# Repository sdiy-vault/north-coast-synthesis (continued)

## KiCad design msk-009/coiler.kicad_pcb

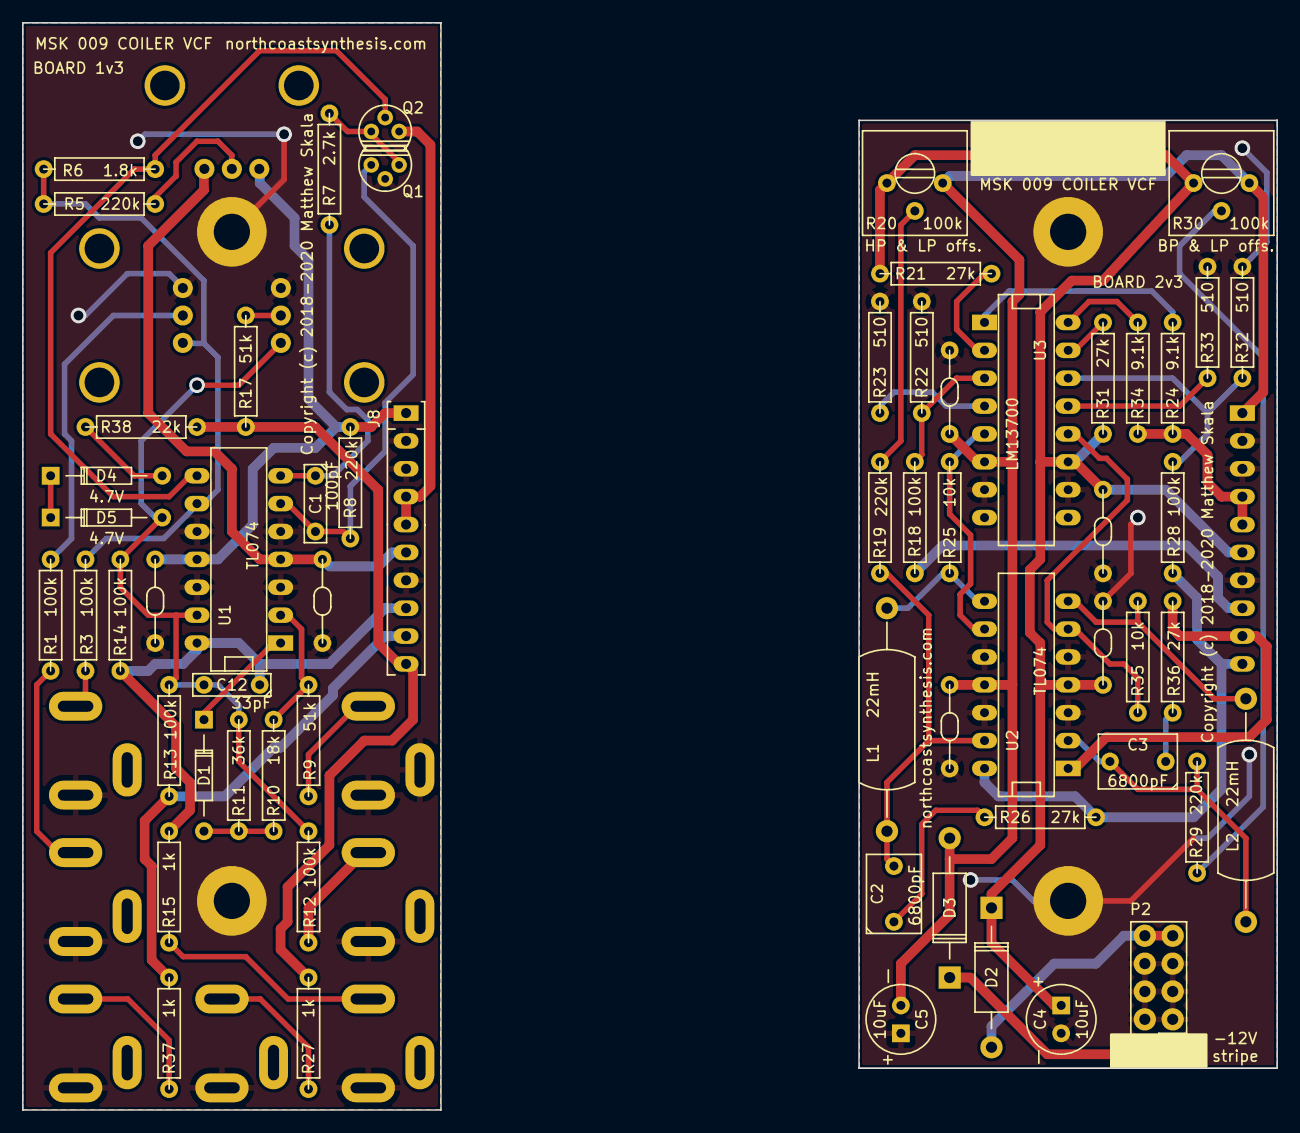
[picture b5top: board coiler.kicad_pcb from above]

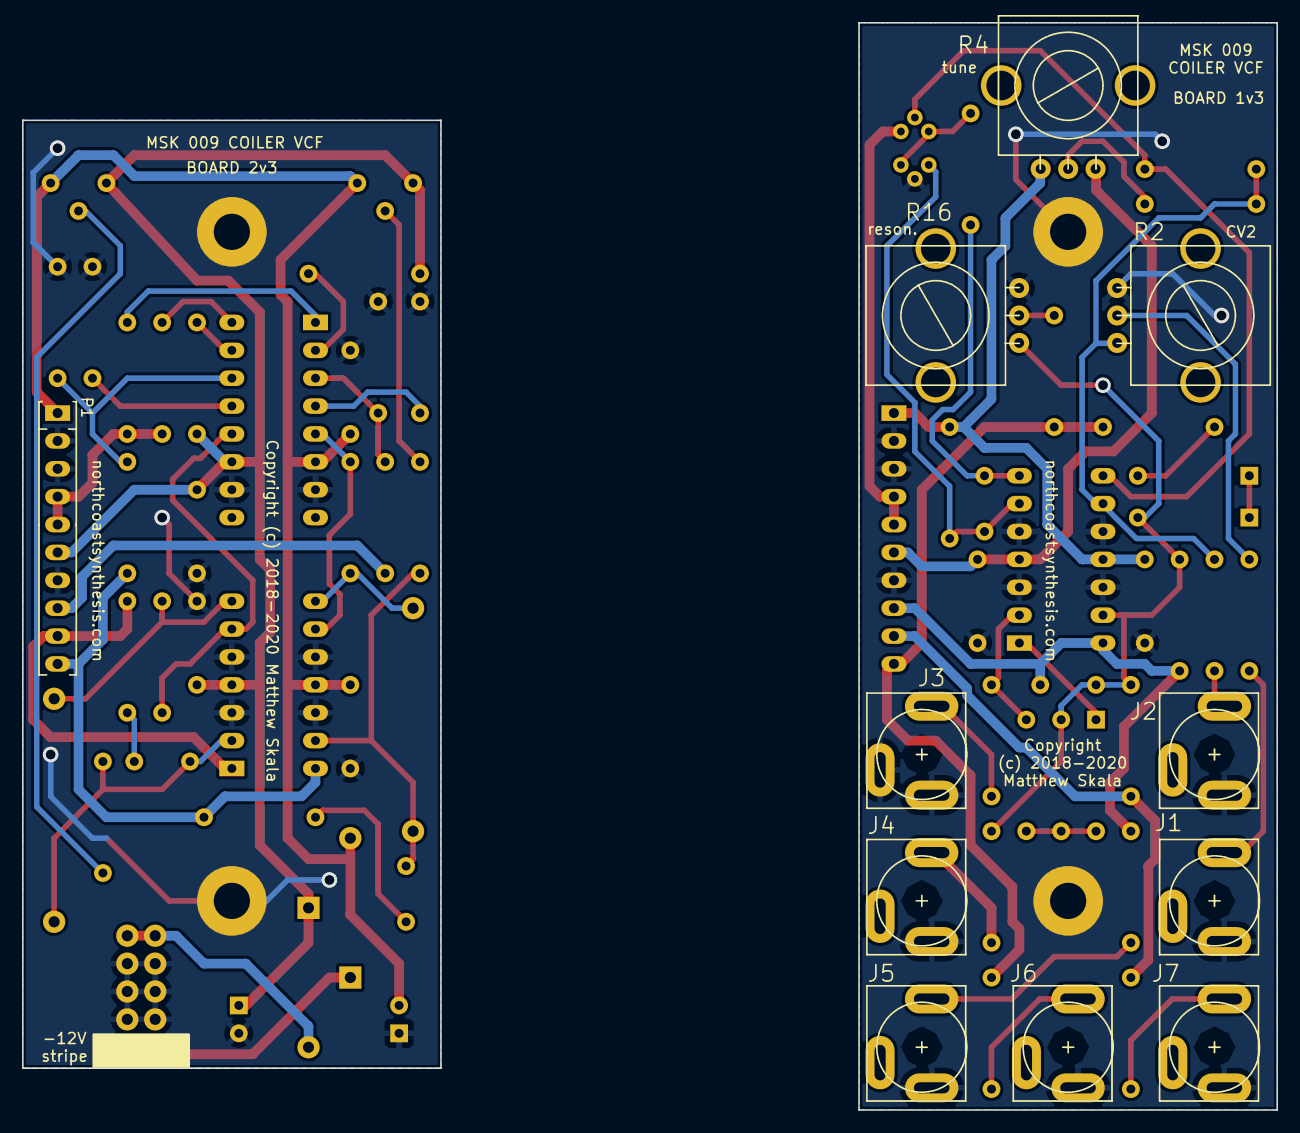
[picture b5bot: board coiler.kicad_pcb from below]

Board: 2 copper layers, 114.3 x 99.1 mm, 76 parts (11 on the bottom side), 48 nets.

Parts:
C1: 100pF; C2msk
C2, C3: 6800pF; C2_3x2msk
C4, C5: 10uF; C1V7msk
C6, C7, C8, C9, C10, C11: 0.1uF; C3msk
C12: 33pF; C2msk
D1: 1N4148; DO35msk
D2, D3: 1N5818; DO15msk
D4, D5: 1N5230B; DO35msk
H5, H6, H9, H10: CONN_01X01; MountingHole_M3
J1, J2, J3, J4, J5, J6, J7: 1502 03; mono_jack_slotted
J8: CONN_01X10; SIP10-socket
L1, L2: 22mH; L8msk
P1: CONN_01X10; SIP10-pins
P2: CONN_02X05; 2x05msk
Q1, Q2: SS8550D; TO92Xmsk
R1, R3, R12, R13, R14, R18, R28: 100k; R4valmsk
R2, R4, R16: 100k; P260Tpot
R5, R8, R19, R29: 220k; R4valmsk
R6: 1.8k; R4valmsk
R7: 2.7k; R4valmsk
R9, R17: 51k; R4valmsk
R10: 18k; R4valmsk
R11: 36k; R4valmsk
R15, R27, R37: 1k; R4valmsk
R20, R30: 100k; 3386Pmsk
R21, R26, R31, R36: 27k; R4valmsk
R22, R23, R32, R33: 510; R4valmsk
R24, R34: 9.1k; R4valmsk
R25, R35: 10k; R4valmsk
R38: 22k; R4valmsk
U1, U2: TL074; DIP14msk
U3: LM13700; DIP16msk

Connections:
+12V: C4.1, C6.2, C8.1, C10.2, D2.2 (K), J8.6, P1.6, R4.3, R20.1, R21.1, R30.1, R31.1, U1.4 (V+), U2.4 (V+), U3.11
-12V: C5.2, C7.2, C9.2, C11.2, D3.1 (A), J8.1, P1.1, R4.1, R8.2, R20.3, R30.3, U1.11 (V-), U2.11 (V-), U3.6 (V-)
/BP: J8.10, P1.10, R17.2, R26.1, R27.2, R28.2, R38.2, U2.14
/CC: J8.4, J8.5, P1.4, P1.5, Q2.3 (C), R24.1, R34.1
/HP: C12.1, J8.8, P1.8, R14.1, R15.2, R18.2, U1.14
/LP: J8.9, P1.9, R13.2, R36.1, R37.2, U2.1
GNDREF: C4.2, C5.1, C6.1, C7.1, C8.2, C9.1, C10.1, C11.1, H5.1, H6.1, H9.1, H10.1, J1.3, J2.3, J3.2, J3.3, J4.3, J5.3, J6.3, J7.3, J8.2, J8.3, J8.7, P1.2, P1.3, P1.7, P2.3, P2.4, P2.5, P2.6, P2.7, P2.8, Q1.2 (B), R2.1, R16.3, R22.2, R23.2, R32.2, R33.2, U1.3 (+), U1.5 (+), U1.10 (+), U1.12 (+), U2.3 (+), U2.5 (+), U2.10 (+), U2.12 (+), U3.7, U3.10
unnamed: C1.1, R7.2, U1.7
unnamed: C1.2, Q1.3 (C), R8.1, U1.6 (-)
unnamed: C2.1, R26.2
unnamed: C2.2, L1.2, R19.1, U2.13 (-)
unnamed: C3.1, R36.2
unnamed: C3.2, L2.2, R29.1, U2.2 (-)
unnamed: C12.2, D5.1 (A), R11.2, R12.1, R13.1, R14.2, R16.1, U1.13 (-)
unnamed: D1.1 (A), R10.1, R11.1
unnamed: D1.2 (K), U1.1
unnamed: D2.1 (A), P2.9, P2.10
unnamed: D3.2 (K), P2.1, P2.2
unnamed: D4.1 (A), R38.1
unnamed: D4.2 (K), D5.2 (K)
unnamed: J1.1, R1.2
unnamed: J2.1, R3.2
unnamed: J3.1, R9.2
unnamed: J4.1, R12.2
unnamed: J5.1, R15.1
unnamed: J6.1, R27.1
unnamed: J7.1, R37.1
unnamed: L1.1, R25.1, U2.8
unnamed: L2.1, R35.1, U2.7
unnamed: Q1.1 (E), Q2.1 (E), R7.1
unnamed: Q2.2 (B), R6.1, U1.8
unnamed: R1.1, R2.2
unnamed: R2.3, R3.1, R5.1, R6.2, U1.9 (-)
unnamed: R4.2, R5.2
unnamed: R9.1, R10.2, U1.2 (-)
unnamed: R16.2, R17.1
unnamed: R18.1, R22.1, U3.3 (+)
unnamed: R19.2, R20.2
unnamed: R21.2, U3.2 (Ibias)
unnamed: R23.1, U3.4 (-)
unnamed: R24.2, U3.1
unnamed: R25.2, U2.9 (-), U3.5
unnamed: R28.1, R32.1, U3.14 (+)
unnamed: R29.2, R30.2
unnamed: R31.2, U3.15 (Ibias)
unnamed: R33.1, U3.13 (-)
unnamed: R34.2, U3.16
unnamed: R35.2, U2.6 (-), U3.12

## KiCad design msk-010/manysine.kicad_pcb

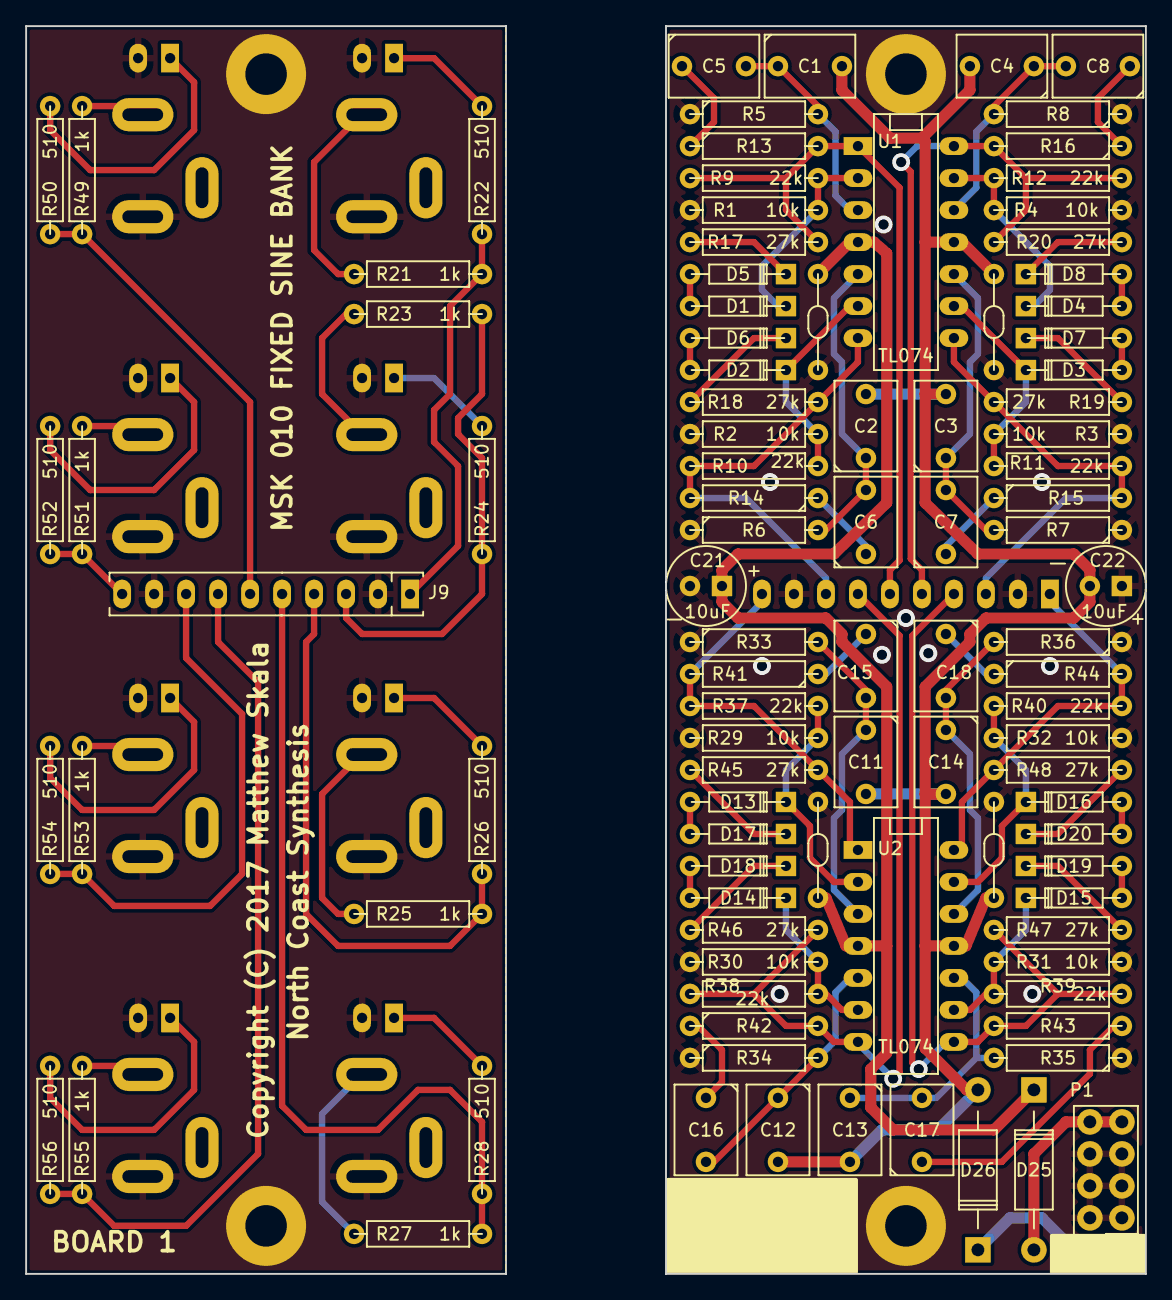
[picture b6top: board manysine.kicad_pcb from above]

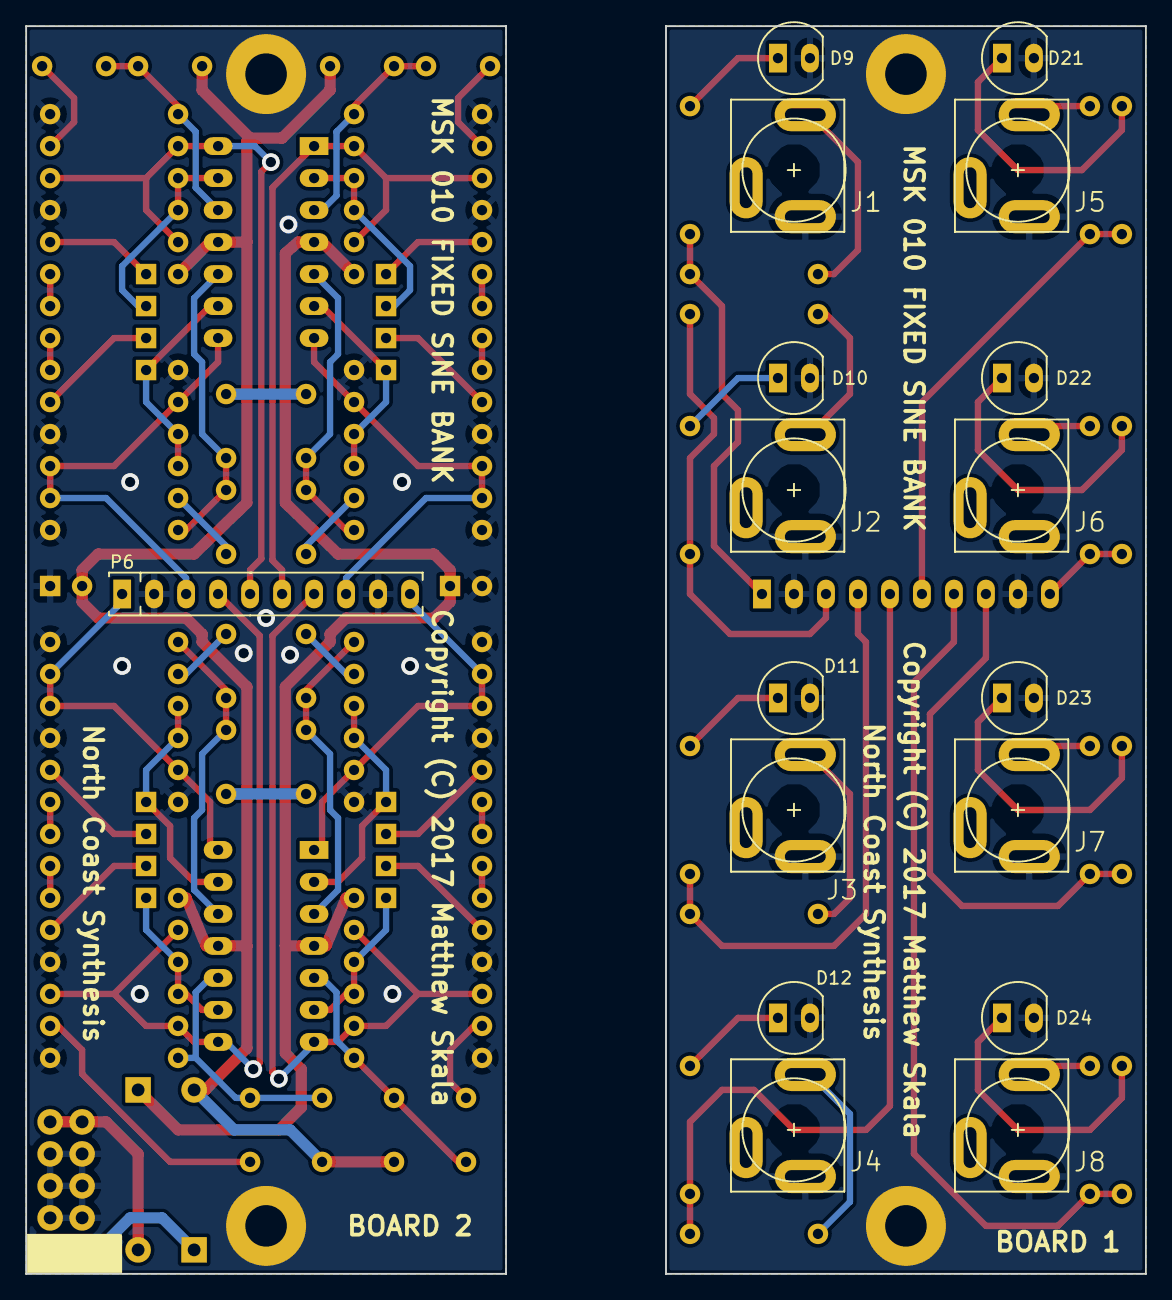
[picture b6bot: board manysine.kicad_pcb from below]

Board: 2 copper layers, 88.9 x 99.1 mm, 121 parts (17 on the bottom side), 69 nets.

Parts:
C1, C2, C3, C4, C5, C6, C7, C8, C11, C12, C13, C14, C15, C16, C17, C18: C; C2_3x2msk
C9, C10, C19, C20: 0.1uF; C3msk
C21, C22: 10uF; C1V7msk
D1, D2, D3, D4, D5, D6, D7, D8, D13, D14, D15, D16, D17, D18, D19, D20: 1N5229B; DO35_3msk
D9, D10, D11, D12, D21, D22, D23, D24: L-57EGW; LEDmsk
D25, D26: 1N5818; DO15msk
H15, H16, H19, H20: CONN_01X01; MountingHole_M3
J1, J2, J3, J4, J5, J6, J7, J8: 1502 03; mono_jack_slotted
J9: CONN_01X10; SIP10msk
P1: CONN_02X05; 2x05msk
P6: CONN_01X10; SIP10msk
R1, R2, R3, R4, R29, R30, R31, R32: 10k; R4valmsk
R5, R6, R7, R8, R13, R14, R15, R16, R33, R34, R35, R36, R41, R42, R43, R44: R; R4msk
R9, R10, R11, R12, R37, R38, R39, R40: 22k; R4valmsk
R17, R18, R19, R20, R45, R46, R47, R48: 27k; R4valmsk
R21, R23, R25, R27, R49, R51, R53, R55: 1k; R4valmsk
R22, R24, R26, R28, R50, R52, R54, R56: 510; R4valmsk
U1, U2: TL074; DIP14msk

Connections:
+12V: C9.2, C19.2, C21.1, D25.2 (K), U1.4 (V+), U2.4 (V+)
-12V: C1.2, C2.2, C3.2, C4.2, C10.2, C11.2, C12.2, C13.2, C14.2, C20.2, C22.2, D26.1 (A), U1.11 (V-), U2.11 (V-)
/OSCA: J9.6, P6.6, R9.2, R13.2, R17.2, R49.1, R50.1, U1.1
/OSCB: J9.8, P6.8, R10.2, R14.2, R18.2, R53.1, R54.1, U1.7
/OSCC: J9.3, P6.3, R11.2, R15.2, R19.2, R23.1, R24.1, U1.8
/OSCD: J9.5, P6.5, R12.2, R16.2, R20.2, R27.1, R28.1, U1.14
/OSCE: J9.10, P6.10, R37.2, R41.2, R45.2, R51.1, R52.1, U2.1
/OSCF: J9.7, P6.7, R38.2, R42.2, R46.2, R55.1, R56.1, U2.7
/OSCG: J9.4, P6.4, R25.1, R26.1, R39.2, R43.2, R47.2, U2.8
/OSCH: J9.1, P6.1, R21.1, R22.1, R40.2, R44.2, R48.2, U2.14
GNDREF: C9.1, C10.1, C19.1, C20.1, C21.2, C22.1, D9.1 (A), D10.1 (A), D11.1 (A), D12.1 (A), D21.1 (A), D22.1 (A), D23.1 (A), D24.1 (A), H15.1, H16.1, H19.1, H20.1, J1.3, J2.3, J3.3, J4.3, J5.3, J6.3, J7.3, J8.3, J9.2, J9.9, P1.3, P1.4, P1.5, P1.6, P1.7, P1.8, P6.2, P6.9, R1.1, R2.1, R3.1, R4.1, R5.1, R6.1, R7.1, R8.1, R29.1, R30.1, R31.1, R32.1, R33.1, R34.1, R35.1, R36.1
unnamed: C1.1, C5.2, R5.2, U1.3 (+)
unnamed: C2.1, C6.2, R6.2, U1.5 (+)
unnamed: C3.1, C7.2, R7.2, U1.10 (+)
unnamed: C4.1, C8.2, R8.2, U1.12 (+)
unnamed: C5.1, R13.1
unnamed: C6.1, R14.1
unnamed: C7.1, R15.1
unnamed: C8.1, R16.1
unnamed: C11.1, C15.2, R33.2, U2.3 (+)
unnamed: C12.1, C16.2, R34.2, U2.5 (+)
unnamed: C13.1, C17.2, R35.2, U2.10 (+)
unnamed: C14.1, C18.2, R36.2, U2.12 (+)
unnamed: C15.1, R41.1
unnamed: C16.1, R42.1
unnamed: C17.1, R43.1
unnamed: C18.1, R44.1
unnamed: D1.1 (A), D5.1 (A)
unnamed: D1.2 (K), R1.2, R9.1, U1.2 (-)
unnamed: D2.1 (A), D6.1 (A)
unnamed: D2.2 (K), R2.2, R10.1, U1.6 (-)
unnamed: D3.1 (A), D7.1 (A)
unnamed: D3.2 (K), R3.2, R11.1, U1.9 (-)
unnamed: D4.1 (A), D8.1 (A)
unnamed: D4.2 (K), R4.2, R12.1, U1.13 (-)
unnamed: D5.2 (K), R17.1
unnamed: D6.2 (K), R18.1
unnamed: D7.2 (K), R19.1
unnamed: D8.2 (K), R20.1
unnamed: D9.2 (K), R22.2
unnamed: D10.2 (K), R24.2
unnamed: D11.2 (K), R26.2
unnamed: D12.2 (K), R28.2
unnamed: D13.1 (A), D17.1 (A)
unnamed: D13.2 (K), R29.2, R37.1, U2.2 (-)
unnamed: D14.1 (A), D18.1 (A)
unnamed: D14.2 (K), R30.2, R38.1, U2.6 (-)
unnamed: D15.1 (A), D19.1 (A)
unnamed: D15.2 (K), R31.2, R39.1, U2.9 (-)
unnamed: D16.1 (A), D20.1 (A)
unnamed: D16.2 (K), R32.2, R40.1, U2.13 (-)
unnamed: D17.2 (K), R45.1
unnamed: D18.2 (K), R46.1
unnamed: D19.2 (K), R47.1
unnamed: D20.2 (K), R48.1
unnamed: D21.2 (K), R50.2
unnamed: D22.2 (K), R52.2
unnamed: D23.2 (K), R54.2
unnamed: D24.2 (K), R56.2
unnamed: D25.1 (A), P1.9, P1.10
unnamed: D26.2 (K), P1.1, P1.2
unnamed: J1.1, R21.2
unnamed: J2.1, R23.2
unnamed: J3.1, R25.2
unnamed: J4.1, R27.2
unnamed: J5.1, R49.2
unnamed: J6.1, R51.2
unnamed: J7.1, R53.2
unnamed: J8.1, R55.2
